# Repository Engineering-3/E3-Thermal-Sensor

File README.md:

E3-Thermal Sensor
========================

This is the thermal sensor used with the Engineering^3 curriculum and RCM Control Stack. Please see [Engineering3](http://engineering3.org/) for more information on the complete RCM Control Stack project.

Repository Contents
-------------------

* **/E3-Thermal-Sensor_v1/** Eagle board/schematic files, gerbers, and BOM

Version History
---------------
* [E3-Thermal-Sensor_v1](https://github.com/Engineering-3/E3-Thermal-Sensor/tree/master/E3-Thermal-Sensor_v1)  Inital relased version v1

License Information
-------------------
Hardware is released under [Solderpad Hardware License v0.51](http://solderpad.org/licenses/SHL-0.51/).
Distributed as-is; no warranty is given.

Getting Started Help
--------------------
This is a Plug-n-Play board.

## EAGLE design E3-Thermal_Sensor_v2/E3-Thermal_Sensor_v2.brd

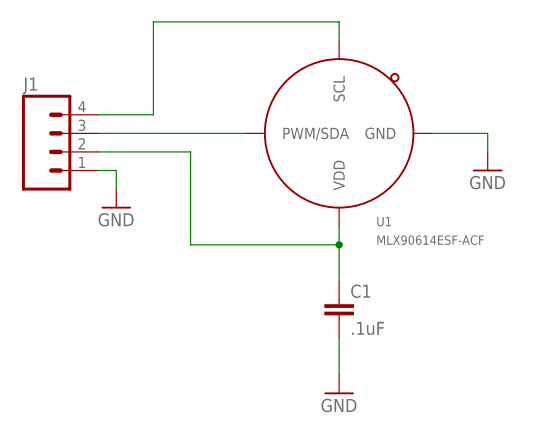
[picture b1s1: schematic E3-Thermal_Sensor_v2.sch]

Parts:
C1: .1uF; 0603-CAP
J1: M04PTH; 1X04
U1: MLX90614ESF-ACF; MLX90614XCF

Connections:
GND: C1.2, J1.1, U1.P4 (GND)
unnamed: C1.1, J1.2, U1.P3 (VDD)
unnamed: J1.3, U1.P2 (PWM/SDA)
unnamed: J1.4, U1.P1 (SCL)

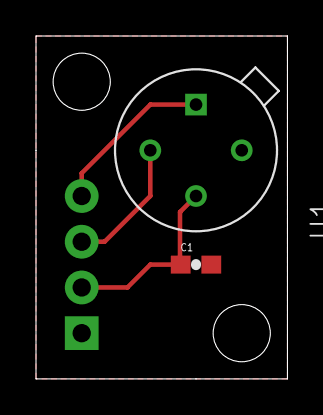
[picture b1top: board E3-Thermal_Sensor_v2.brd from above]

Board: 2 copper layers, 14.0 x 19.1 mm, 3 parts (1 on the bottom side), 4 nets.

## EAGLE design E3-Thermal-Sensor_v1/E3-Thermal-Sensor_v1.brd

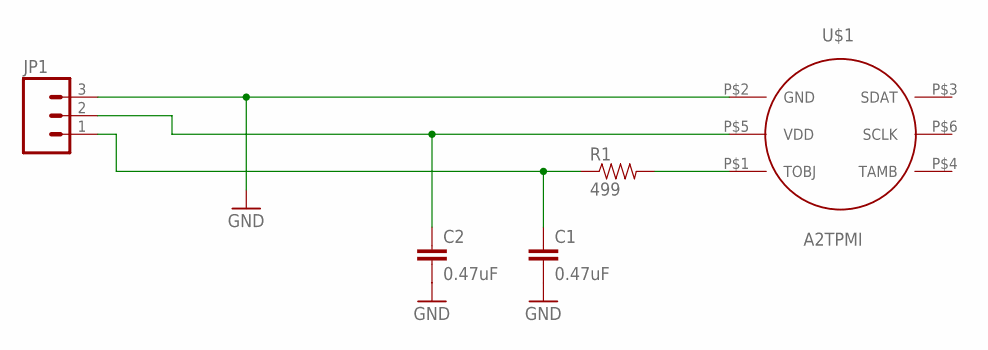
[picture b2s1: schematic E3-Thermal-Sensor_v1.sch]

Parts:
C1, C2: 0.47uF; C0402
JP1: M03PTH; 1X03
R1: 499; C0402
U$1: A2TPMI

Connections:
GND: C1.2, C2.2, JP1.3, U$1.P$2 (GND)
unnamed: C1.1, JP1.1, R1.1
unnamed: R1.2, U$1.P$1 (TOBJ)
unnamed: C2.1, JP1.2, U$1.P$5 (VDD)

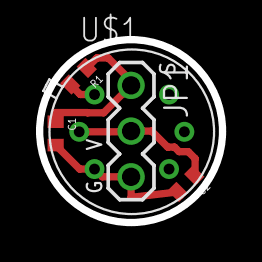
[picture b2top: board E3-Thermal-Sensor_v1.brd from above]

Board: 2 copper layers, 10.2 x 10.2 mm, 5 parts (0 on the bottom side), 4 nets.

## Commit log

2015-02-18 Initial file checkin.
2015-02-18 Added BOM from Jim.
2015-02-19 Added readme file.
2015-02-19 Renamed readme.
2017-05-28 Adding new v2 of the Thermal Sensor board.
2017-07-14 V2 of Thermal Sensor board.
2017-08-07 Final version sent to fab.
2017-12-04 Added dimensions.
2017-12-04 Added more dimensions.
2017-12-10 With new test56 firmware, got Thermal Sensor address re-writing working. Use PicoCAddressScanner.c to see what address your sensor(s) are at. Use PicoCSetAddress.c to change the address of a sensor U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
2017-12-10 Updated list of no-no addresses for I2C bus.
2019-10-17 Updated address scanner PicoC program to work properly with new I2C return value.

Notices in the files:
E3-Thermal-Sensor_v1/E3-Thermal-Sensor_v1.sch:
Copyright 2015 Engineering^3 LLC
Copyright 2015 Engineering^3 LLC Copyright and related rights are licensed under the Solderpad Hardware License,
Version 0.51 (the “License”); you may not use this file except in compliance with the License. You may obtain a copy
parts and their libraries:
SparkFun-Connectors: Licensing: Creative Commons ShareAlike 4.0 International - https://creativecommons.org/licenses/by-sa/4.0
